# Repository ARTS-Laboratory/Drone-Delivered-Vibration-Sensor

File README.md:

# Drone Delivered Vibration Sensor
UAV deployable sensor package for vibration-based structural health monitoring.

<p align="center">
  
</p>
<p align="center">
Figure 1: Video of UAV deploying a sensor package in the Rock Branch Creek at the University of South Carolina. UAV under manual control. Click the image to view the video on YouTube. 
</p>

## [System Design](System_design)
Vibration sensor package: includes sensor package software (Arduino) and hardware (circuit) files along with package frame design.

<br /><br /><br />

## Licensing and Citation

[![CC BY-SA 4.0][cc-by-sa-shield]][cc-by-sa]

This work is licensed under a
[Creative Commons Attribution-ShareAlike 4.0 International License][cc-by-sa].

[cc-by-sa]: http://creativecommons.org/licenses/by-sa/4.0/
[cc-by-sa-image]: https://licensebuttons.net/l/by-sa/4.0/88x31.png
[cc-by-sa-shield]: https://img.shields.io/badge/License-CC%20BY--SA%204.0-lightgrey.svg

Cite as:

@Misc{ARTSLabDroneDeliveredVibration,     
  author = {{ARTS-L}ab},  
  howpublished = {GitHub},    
  title  = {Drone Delivered Vibration Sensor},    
  groups = {{ARTS-L}ab},    
  url    = {https://github.com/ARTS-Laboratory/Drone-Delivered-Vibration-Sensor},   
  note = {Accessed: Month dd, yyyy},   
}

<p align="center">
QR code for repo.
</p>

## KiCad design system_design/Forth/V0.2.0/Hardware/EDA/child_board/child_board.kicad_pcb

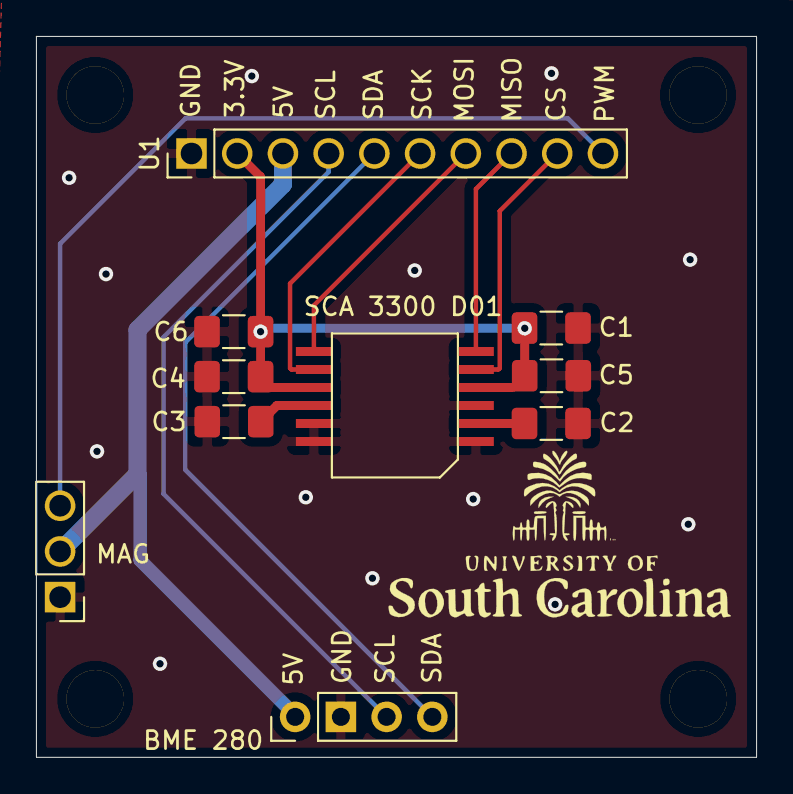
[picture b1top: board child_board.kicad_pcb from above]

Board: 2 copper layers, 40.0 x 40.0 mm, 15 parts (0 on the bottom side), 12 nets.

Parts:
., .#2, .#3, .#5: MountingHole_3.2mm_M3_DIN965_Pad
.#4: .; uofsc_logo_0_75in
BME 280: BME; PinHeader_1x04_P2.54mm_Vertical
C1, C2, C3, C4, C5, C6: C_Small; C_1206_3216Metric_Pad1.42x1.75mm_HandSolder
MAG: Conn_01x03_Female; PinHeader_1x03_P2.54mm_Vertical
SCA 3300 D01: SCA_330_X1; SCA-3300 X1
U1: 10PinConnector; PinHeader_1x10_P2.54mm_Vertical

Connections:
+3V3: C1.1, C4.1, C5.2, C6.1, SCA 3300 D01.4, SCA 3300 D01.9, U1.2
GND: BME 280.2, C1.2, C2.1, C3.1, C4.2, C5.1, C6.2, MAG.1, SCA 3300 D01.1, SCA 3300 D01.3, SCA 3300 D01.11, SCA 3300 D01.12, U1.1
unnamed: C2.2, SCA 3300 D01.2
unnamed: C3.2, SCA 3300 D01.10
unnamed: BME 280.1, MAG.2, U1.3
unnamed: MAG.3, U1.10
unnamed: BME 280.3, U1.4
unnamed: BME 280.4, U1.5
unnamed: SCA 3300 D01.8, U1.6
unnamed: SCA 3300 D01.7, U1.7
unnamed: SCA 3300 D01.6, U1.8
unnamed: SCA 3300 D01.5, U1.9

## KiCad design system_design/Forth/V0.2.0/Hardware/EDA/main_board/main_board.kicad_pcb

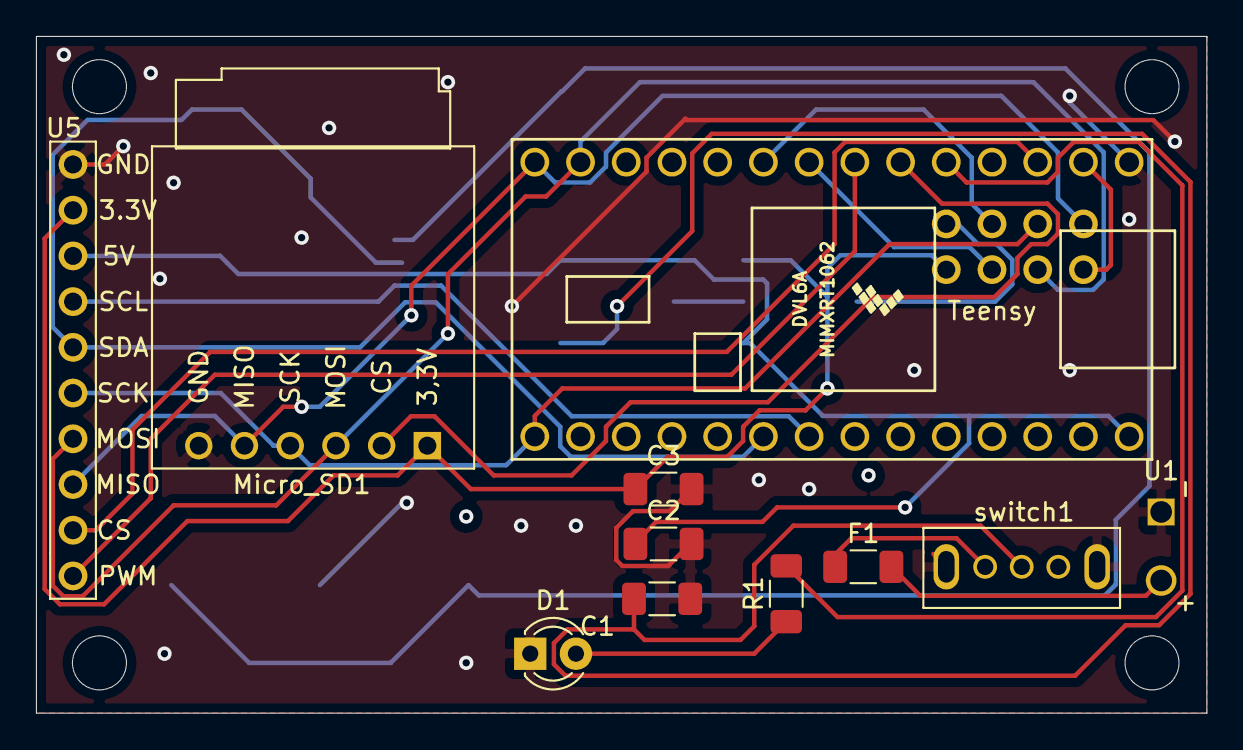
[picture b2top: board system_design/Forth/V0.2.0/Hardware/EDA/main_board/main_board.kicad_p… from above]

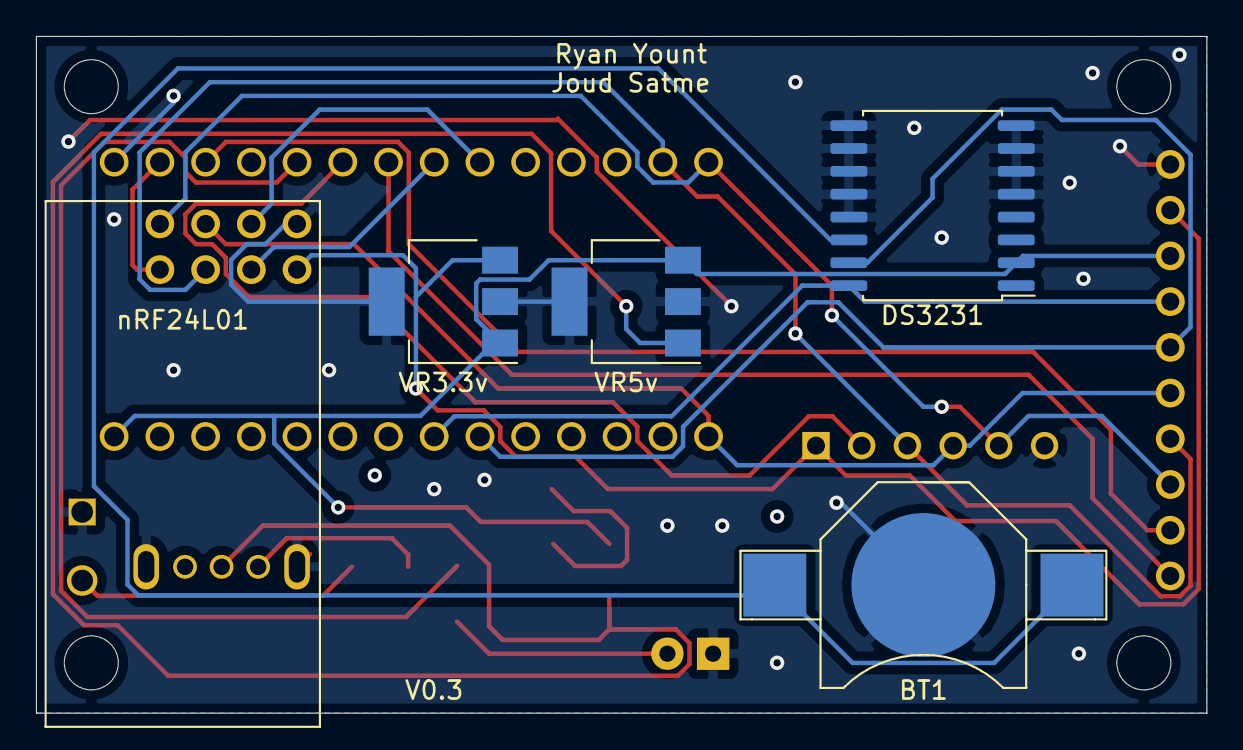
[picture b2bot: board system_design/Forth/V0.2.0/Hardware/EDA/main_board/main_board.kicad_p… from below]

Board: 2 copper layers, 65.0 x 37.6 mm, 16 parts (5 on the bottom side), 20 nets.

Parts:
BT1: Battery_Cell; battery_holder_10mm
C1, C2, C3: C; C_1206_3216Metric_Pad1.33x1.80mm_HandSolder
D1: LED; LED_D3.0mm
DS3231: DS3231M; SOIC-16W_7.5x10.3mm_P1.27mm
F1: Fuse; C_1206_3216Metric_Pad1.33x1.80mm_HandSolder
Micro_SD1: microSD_small; small_microSD_v2
R1: R; R_1206_3216Metric_Pad1.30x1.75mm_HandSolder
Teensy: Teensy4.0-teensy; teensy4.0
U1: power_input; XT60PW
U5: main_board_top_rail; top_rail
VR3.3v, VR5v: AP7361C-33E; SOT-223-3_TabPin2
nRF24L01: nRF24L01+
switch1: grounded_DIP_switch; grounded_switch

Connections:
GND: BT1.2, C1.2, C2.2, C3.2, D1.1, DS3231.5, DS3231.6, DS3231.7, DS3231.8, DS3231.9, DS3231.10, DS3231.11, DS3231.12, DS3231.13, Micro_SD1.6, Teensy.1, U1.1, U5.9, VR3.3v.2, VR5v.2, nRF24L01.5, switch1.4, switch1.5
unnamed: BT1.1, DS3231.14
unnamed: C1.1, VR5v.1, switch1.2
unnamed: C2.1, DS3231.2, Teensy.33, U5.7, VR3.3v.1, VR5v.3
unnamed: C3.1, Micro_SD1.1, U5.8, VR3.3v.3, nRF24L01.1
unnamed: D1.2, R1.1
unnamed: F1.1, switch1.1
unnamed: F1.2, U1.2
unnamed: Micro_SD1.2, Teensy.6
unnamed: Micro_SD1.3, Teensy.13, U5.3, nRF24L01.3
unnamed: Micro_SD1.4, Teensy.20, U5.4, nRF24L01.7
unnamed: Micro_SD1.5, Teensy.14, U5.2, nRF24L01.8
unnamed: R1.2, Teensy.5
unnamed: Teensy.2, nRF24L01.4
unnamed: Teensy.3, U5.1
unnamed: Teensy.7, U5.10
unnamed: Teensy.8, nRF24L01.2
unnamed: Teensy.9, nRF24L01.6
unnamed: DS3231.15, Teensy.25, U5.5
unnamed: DS3231.16, Teensy.26, U5.6

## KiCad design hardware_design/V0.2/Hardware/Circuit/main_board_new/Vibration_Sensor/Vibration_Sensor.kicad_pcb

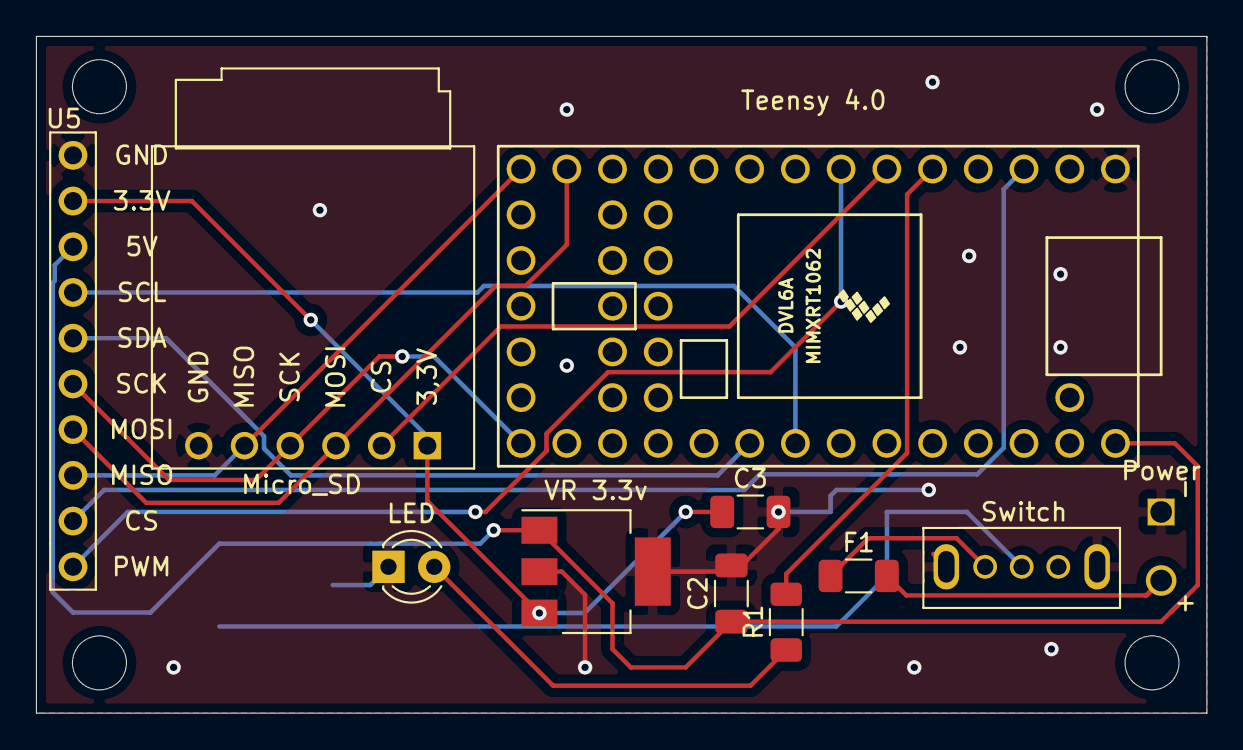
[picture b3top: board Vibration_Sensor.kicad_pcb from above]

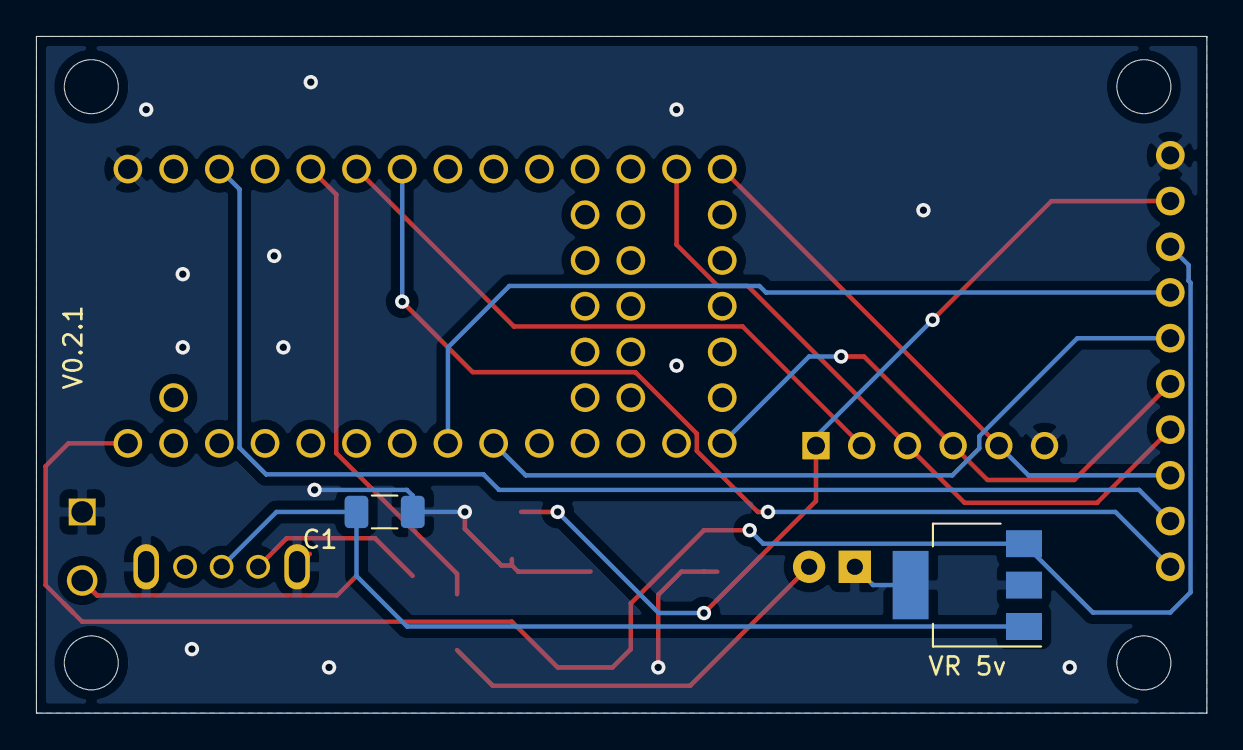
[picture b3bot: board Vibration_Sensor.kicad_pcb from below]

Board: 2 copper layers, 65.0 x 37.6 mm, 13 parts (3 on the bottom side), 16 nets.

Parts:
C1, C2, C3: C; C_1206_3216Metric_Pad1.33x1.80mm_HandSolder
F1: Fuse; C_1206_3216Metric_Pad1.33x1.80mm_HandSolder
LED: LED; LED_D3.0mm
Micro_SD: microSD_small; small_microSD_v2
Power: power_input; XT60PW
R1: R; R_1206_3216Metric_Pad1.30x1.75mm_HandSolder
Switch: grounded_DIP_switch; grounded_switch
Teensy 4.0: Teensy4.0-teensy; Teensy40
U5: main_board_top_rail; top_rail
VR 3.3v, VR 5v: AP7361C-33E; SOT-223-3_TabPin2

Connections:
GND: C1.2, C2.2, C3.2, LED.1, Micro_SD.6, Power.1, Switch.4, Switch.5, Teensy 4.0.1, U5.9, VR 3.3v.2, VR 5v.2
unnamed: C1.1, Switch.2, VR 5v.1
unnamed: C2.1, Teensy 4.0.33, U5.7, VR 3.3v.1, VR 5v.3
unnamed: C3.1, Micro_SD.1, U5.8, VR 3.3v.3
unnamed: LED.2, R1.1
unnamed: F1.1, Switch.1
unnamed: F1.2, Power.2
unnamed: Micro_SD.2, Teensy 4.0.6
unnamed: Micro_SD.3, Teensy 4.0.13, U5.3
unnamed: Micro_SD.4, Teensy 4.0.20, U5.4
unnamed: Micro_SD.5, Teensy 4.0.14, U5.2
unnamed: R1.2, Teensy 4.0.5
unnamed: Teensy 4.0.3, U5.1
unnamed: Teensy 4.0.7, U5.10
unnamed: Teensy 4.0.25, U5.5
unnamed: Teensy 4.0.26, U5.6

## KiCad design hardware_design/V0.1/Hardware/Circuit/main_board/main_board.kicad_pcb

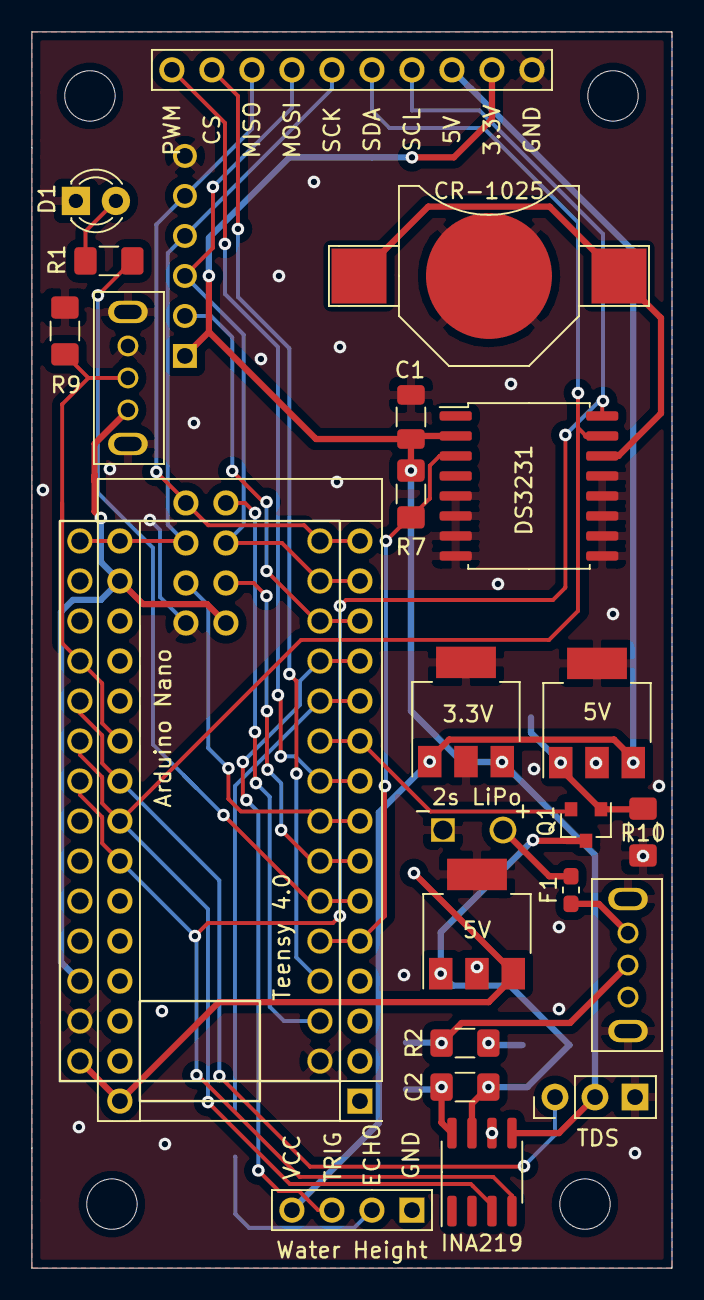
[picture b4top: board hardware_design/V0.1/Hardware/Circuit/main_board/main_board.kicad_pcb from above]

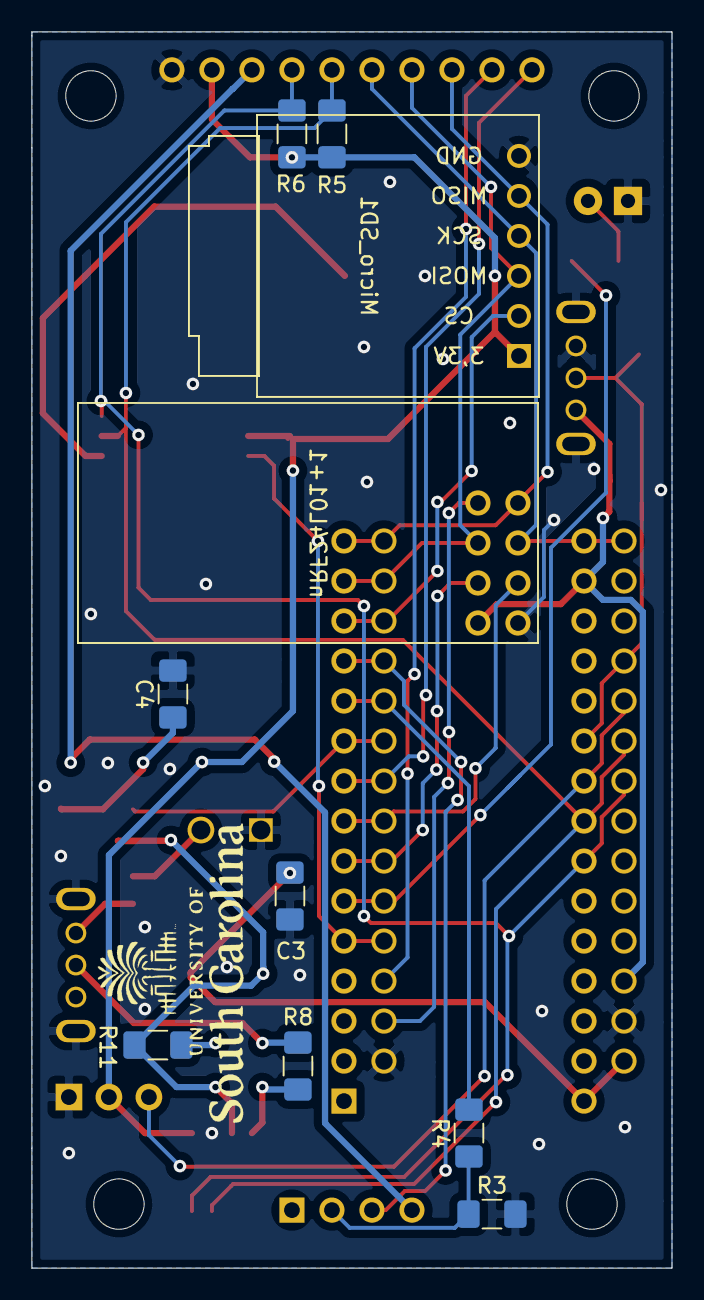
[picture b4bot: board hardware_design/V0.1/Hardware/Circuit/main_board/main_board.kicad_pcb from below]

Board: 2 copper layers, 40.6 x 78.5 mm, 34 parts (8 on the bottom side), 33 nets.

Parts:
2s LiPo: XP60PW; XT60PW
3.3V, 5V, 5V#2: KA78M05_TO252; SOT-223-3_TabPin2
Arduino Nano: Arduino_Nano_v2.x-MCU_Module; Arduino_Nano
C1: C; R_1206_3216Metric
C2, C3, C4: C; R_1206_3216Metric_Pad1.42x1.75mm_HandSolder
CR-1025: Battery_Cell; battery_holder_10mm
D1: LED; LED_D3.0mm
DS3231: DS3231M; SOIC-16W_7.5x10.3mm_P1.27mm
F1: Fuse; R_0603_1608Metric_Pad1.05x0.95mm_HandSolder
INA219: INA219AxD; SOIC-8_3.9x4.9mm_P1.27mm
Micro_SD1: small_microSD
Q1: 2N2219; SOT-23
R1: 1k; R_1206_3216Metric_Pad1.42x1.75mm_HandSolder
R2: Rs; R_1206_3216Metric_Pad1.42x1.75mm_HandSolder
R3, R4: 2.2k; R_1206_3216Metric_Pad1.42x1.75mm_HandSolder
R5, R6, R7: 4.7k; R_1206_3216Metric_Pad1.42x1.75mm_HandSolder
R8, R11: 10; R_1206_3216Metric_Pad1.42x1.75mm_HandSolder
R9, R10: 10k; R_1206_3216Metric_Pad1.42x1.75mm_HandSolder
TDS: tds_3pin; PinHeader_1x03_P2.54mm_Vertical
Teensy 4.0: Teensy4.0; teensy4.0
Water Height: HCSR04
nRF24L01+1: nRF24L01+
switch1: grounded_switch
switch2: grounded_DIP_switch; grounded_switch
top_rail1: top_rail

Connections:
GND: 2s LiPo.1, 3.3V.2, 5V.2, 5V#2.2, C1.2, C3.1, C4.2, CR-1025.2, D1.1, DS3231.5, DS3231.6, DS3231.7, DS3231.8, DS3231.9, DS3231.10, DS3231.11, DS3231.12, DS3231.13, INA219.6, Micro_SD1.6, R3.2, R9.2, R10.1, TDS.3, Teensy 4.0.1, Teensy 4.0.32, nRF24L01+1.5, switch1.4, switch1.5, switch2.3, switch2.4, switch2.5, top_rail1.9
unnamed: Arduino Nano.5, DS3231.3, R7.2, Teensy 4.0.4
unnamed: Arduino Nano.6, R1.1, Teensy 4.0.5
unnamed: Arduino Nano.7, Teensy 4.0.6, nRF24L01+1.2
unnamed: Arduino Nano.8, Teensy 4.0.7, nRF24L01+1.6
unnamed: Arduino Nano.9, Teensy 4.0.8, top_rail1.10
unnamed: Arduino Nano.10, Q1.2, Teensy 4.0.9
unnamed: Arduino Nano.11, R4.2, Teensy 4.0.10
unnamed: Arduino Nano.12, Teensy 4.0.11, Water Height.3
unnamed: Arduino Nano.13, Micro_SD1.2, Teensy 4.0.12
unnamed: Arduino Nano.14, Micro_SD1.3, Teensy 4.0.13, nRF24L01+1.3, top_rail1.3
unnamed: Arduino Nano.15, Micro_SD1.5, Teensy 4.0.14, nRF24L01+1.8, top_rail1.2
unnamed: Arduino Nano.16, Micro_SD1.4, Teensy 4.0.20, nRF24L01+1.7, top_rail1.4
unnamed: Arduino Nano.17, Teensy 4.0.31, nRF24L01+1.1, switch2.1
unnamed: Arduino Nano.21, R9.1, Teensy 4.0.23, switch2.2
unnamed: Arduino Nano.22, TDS.1, Teensy 4.0.24
unnamed: Arduino Nano.23, DS3231.15, INA219.3, R5.2, Teensy 4.0.25, top_rail1.5
unnamed: Arduino Nano.24, DS3231.16, INA219.4, R6.2, Teensy 4.0.26, top_rail1.6
unnamed: 5V.3, Arduino Nano.30, C3.2, Teensy 4.0.33
unnamed: CR-1025.1, DS3231.14
unnamed: 3.3V.3, C1.1, DS3231.2, INA219.5, Micro_SD1.1, R5.1, R6.1, R7.1, TDS.2, top_rail1.8
unnamed: C2.1, INA219.8, R8.1
unnamed: 5V.1, C2.2, INA219.7, Q1.3, R11.1
unnamed: 5V#2.1, C4.1, Q1.1, R10.2
unnamed: D1.2, R1.2
unnamed: F1.1, switch1.1
unnamed: 2s LiPo.2, F1.2
unnamed: R2.1, R8.2, switch1.2
unnamed: R3.1, R4.1, Water Height.2
unnamed: R2.2, R11.2
unnamed: Teensy 4.0.2, nRF24L01+1.4
unnamed: Teensy 4.0.3, top_rail1.1
unnamed: 3.3V.1, 5V#2.3, Water Height.4, top_rail1.7

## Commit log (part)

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2020-11-02 Add .gitignore and .gitattributes.
2020-11-02 Add project files.
2020-11-04 update pins
2020-11-16 tested
2020-11-17 record time stamp instead of calculating frequency
2020-11-17 print frequency
2022-05-23 Update VibrationSensor.ino
    submission
2022-05-24 software
2022-05-24 version control
2022-05-24 package
2022-05-24 SCA library
2022-05-27 Created V0.2
2022-05-30 cleaned up repo for EMI 2022.
2022-06-09 Updated markdown
2022-06-13 New transceiver code (just LED)
2022-07-06 Beam test analysis
2022-07-07 Updated kicad and beam testing files
2022-08-16 tests
    added experimental data
2022-08-16 updated readme for data
2023-01-23 PCB changes
2023-03-11 Changed folder name to fit the test
    The excitation you used is an impulse response.
    Driven excitation is for sinusoidal
2023-05-29 Added files for version 0.5
2023-06-23 Changed V0.5 PCB
2024-04-05 updated VI
2024-04-05 ignore error file
2024-05-14 signal processing transfer
2024-05-14 Update README.md
    cleaned up read me
2024-06-26 added Bayonne for LSTM project
    Create README.md
    Update README.md
2024-07-02 Prepared LSTM and Model
    This commit contains the LSTM implementation, the model weights in .csv
    format, and a script to generate a C++ header file to load the weights
    on the Teensy. The output is in model-weights.h.
2024-07-22 Removed LSTM Folder
    This folder will be redundant and is not required
2024-07-22 Retrained Model
2024-07-23 Removed linear approximation
    Linear approximation of activation functions is promising, but it would
    be best to stay on topic for this paper. We'll just use the Arduino math
    library for now and save linear approximation for another time.
2024-07-23 Changed LSTM latency output unit
    Changed the unit used to measure how long it takes to process the
    accelerometer data from microseconds to milliseconds. Fixed a few
    missing escape characters.
2024-07-23 Activation function fix
    Fixes an error in the activation function logic and ensures arrays are
    initialized to zero. Parity has been achieved with the model running
    through Keras.
2024-07-23 Copyright message
    Added the word "copyright" to the copyright message. Better safe than
    sorry.
2024-07-24 Offset acceleration
    The model was trained with normalized acceleration data, so we must
    subtract 1 from the G's experienced by the sensor package to do
    inference properly.
2024-07-24 Fixed activation functions
    Fixed the issue with the activation functions that was causing the
    exploding initial state problem. This has been tested, compared against
    the same data running through Keras, and shown to be effective.
2024-07-29 Forward pass function
    Created a function for the forward pass to avoid programming errors
2024-07-29 Removed timestamps
    Timestamps will no longer be recorded
2024-07-29 More accurate sampling logic
    Changed the way the sampling delay is implemented to get get closer to
    the target frequency
2024-07-29 Reset LSTM state after data processing
    LSTM now enters every trial in its initial state to prevent accuracy
    loss as the program continues to run.
2024-08-05 Readability improvements
    Small things to make the code more professional and easier to work on.
2024-08-05 Remove redundant trigger mechanism
    If we need this, we can put something similar back in when the time
    comes.
2024-08-07 New firmware for dataset collection
    Initial commit for a new firmware specificaly for dataset collection.
    For various reasons, this is easier and more accurate than using
    lstm-compensation and removing the compensated data in post. Should also
    be a bit better for our purposes than the Brooklyn version.
2024-08-07 Renamed a folder
2024-08-09 Header generation logic overhaul
    The logic for converting the weight CSVs into a C header file has been
    reworked. No new features have been added yet, but this is a stepping
    stone for doing the preprocessing here instead of in the model's
    training code.
2024-08-12 Fix output directory
    Accidentally outputted to a test file instead of the actual header file.
2024-08-12 Handle directory errors
    Adds a message for when this script is being run from the wrong place or
    when some weight files are missing. Hopefully stuff like this helps
    future ARTS people build off my code.
2024-08-14 Weight preprocessing
    The header generation script now accepts weights taken directly from
    keras. Previously, I had to modify the training script to get the
    weights in the correct format, but it makes more sense to do it here
    because the weight format is inherent to the implementation and not the
    model itself.
2024-08-21 Updated weight format
    The new script expects the W and U matrices to be in seperate CSVs.
2024-08-21 Removed timestamp remnant
2024-09-19 Trigger for data collection
2024-09-19 Reimplement timestamps
    By recording a timestamp, sampling the accelerometer, then recording
    another timestamp, an average timestamp can be calculated for each
    datapoint that will be more reflective of the actual time the sample was
    taken.
2024-10-08 Fix truncation issue
    Print the full precision of the float
2024-10-08 Change number of samples per test
2024-10-17 Larger buffer w/ memory hack
    A combination of static and dynamic memory allocation will allow us to
    split the timestamp and datapoint buffers between the Teensy's two RAM
    banks. This gets us to 75s per recording.
2024-10-29 Rework interpolation strategy
    If we tried to interpolate the who array, we would use up too much
    memory. We'll have to do it one point at a time.
2024-10-29 Interpolate input data
    Input data is now interpolated prior to inference. The memory penalty
    has been mitigated somewhat, but we're using twice as much memory to
    store the datapoints compared to what we would have been otherwise. It
    will be worth it.
2024-11-06 Fix errors
2024-12-07 Remove interpolation
    Since we're recording at a much lower sample rate, the small variations
    in sample timing are negligable, making linear interpolation unnecessary
2024-12-07 Lower data collection sample rate
2025-03-23 Create reduced lstm firmware
2025-03-25 Update weights + add reduced model
2025-05-15 Wait for trigger to record
    Previous logic would send out a trigger signal to the NI setup to begin
    the reference accelerometer. Now, both accelerometers will wait for an
    external trigger signal emitted by switch or button.
2025-05-20 DoF operations
    Added the DoF matvec to the improved linear algebra library for use in a
    DoF LSTM.
2025-05-20 Fix typo
2025-05-23 Seperate gate vectors
    For clarity, the gate vectors have been seperated. This won't have a
    significant impact as long as the DoF lstm follows suit, which it will.
2025-05-23 Swap rows and columns in matvec signature
    The logic here is correct, but the positional arguments led to some
    confusion.
2025-05-23 Split bias vectors
    Along the same motivation as splitting the gates.
2025-05-23 Implement LSTM
    A much cleaner LSTM than V0.1.
2025-05-28 loadWeights() implementation
2025-05-28 Initialize LSTM
2025-05-29 Fix dense bias bug
2025-05-29 Fix bug in dot()
2025-05-30 Testing data generation
    Like the code says, this is not for testing the accuracy of the model,
    but rather making sure the implementation is working as it should. When
    the model isn't working properly, it won't produce anything remotely
    like the input data.
2025-05-30 Header guard
2025-06-02 Complete LSTM test program
    There's some cleaning up to do, but this will help us fix the problem
    we're having on the teensy, which is more important.
2025-06-02 Use real data for testing
2025-06-03 Fix bias array size
2025-06-03 Remove file read debug prints
2025-06-03 Better output formatting
2025-06-03 Update model with new exporting technique
2025-06-03 Fix dot product bug
2025-06-03 Fix bug in dataset loading
2025-06-03 Fix nondeterministic behavior
2025-06-04 Organize tests
2025-06-04 Fix LSTM
    The LSTM has been verified to be working using the testbench.
2025-06-05 Fix weight loading bug
    At this point, the system is fully functional.
2025-06-30 Fix DoF dimension arguments
2025-07-01 file updates
2025-07-01 Add test model and data for reduced LSTM
2025-07-01 Load reduced LSTM model
2025-07-01 Add reduced test out
2025-07-01 Fix incorrect index for DoF matvec
2025-07-01 Remove data generation
    The testing workflow no longer requires the use of generated data.
2025-07-01 Generalize matrix dimensions
2025-07-08 Fix DoF LSTM
    Unfortunately, this will be another mega-commit. Changes include
    splitting the b and c weight files, fixing a bug that caused the c state
    to not be written properly, updating the testing model, and fixing DoF
    weight matrix dimensions.
2025-07-10 Use merged weight matrices
    Both the reduced and non-reduced models now use the merged weight matrix
    for parity.
2025-07-18 Reduced LSTM firmware
    This is tested to be working. In the future, the rank will be loaded
    from the SD card as well. The idea is that all reduced models will use
    the same firmware so we don't recompile every time we need to swap out
    the model. We'll need to do this a lot. Maybe even 50 times.
2025-07-18 Definitions
2026-03-16 Proposed update to dataset-collection.ino
    See the README file
2026-05-01 started V0.1 and v0.2 of Forth
2026-05-01 file oorganization
2026-05-01 file clean up
2026-05-01 child board works at this point
2026-05-01 added kicad number
2026-05-01 added BOM
2026-05-01 updated gitignore
2026-05-01 added prl to gitignore
2026-05-01 silk screen update
2026-05-02 moved .lib and .dcm files into "libraries".
2026-05-12 Updates to shaker data collection code
2026-05-12 removed draft BOM
2026-05-12 deleted bench top experimental code
2026-05-12 Altered version of code to account for offset axis among the two accelerometers
2026-05-12 Update DataCollection_DifferentAxis.ino
    Alteration to code to account for different axis direction
2026-05-12 Updated BOM
2026-05-13 Updated code for changing axis orientation
2026-05-18 Data Collection Graphs
2026-05-19 Latest shaker data collection
2026-05-19 Work in-progress code for shaker data collection
2026-05-20 updated sensor frame to include permanent magnet cap
2026-06-02 added self diagnose code
2026-06-05 File Organization
2026-06-09 arduino code new version
2026-06-09 modified cad model
2026-06-09 Changes to LED code
2026-06-09 Merging code with VibrationSensor arduino code (in progress)
2026-06-10 Experimental data upload from SD cards
2026-06-10 stl file
2026-06-10 step file
2026-06-10 Images of in-progress designs
2026-06-10 Updated Magnet Cap
2026-06-10 working code
2026-06-11 trigger code
2026-06-11 3D print attempts for magnet cap
2026-06-11 Added code responsible for switching accelerometer axis
2026-06-11 Updated magnet cap dimensions and spectrogram image (test run)
2026-06-11 mods
2026-06-12 Switched from bottom sensor axis to top sensor axis
2026-06-12 New data graphing code
2026-06-12 Updated data collection size
2026-06-12 Experiment data - finding data point threshold
2026-06-12 CSV data files
2026-06-14 High-pass filter applied to graphing code & re-organized folders
2026-06-15 LSTM netowrk addition to graphing code
2026-06-15 First attempt - LSTM network code
2026-06-16 Updated lstm code and graphing results
2026-06-16 Re-run of lstm network
2026-06-17 Updated lstm code - FRF graphing code added
2026-06-18 LSTM results - 100 epoch
2026-06-23 Updated shaker graphing code - training multiple csv files
2026-06-23 Attempt at new lstm recordings
2026-06-24 Organizing - Separating new code graphs from old code
2026-06-25 Epoch 20, Batch size 16, window size 400
2026-06-25 Updated code - files sent to dropbox
2026-06-25 updated window size
